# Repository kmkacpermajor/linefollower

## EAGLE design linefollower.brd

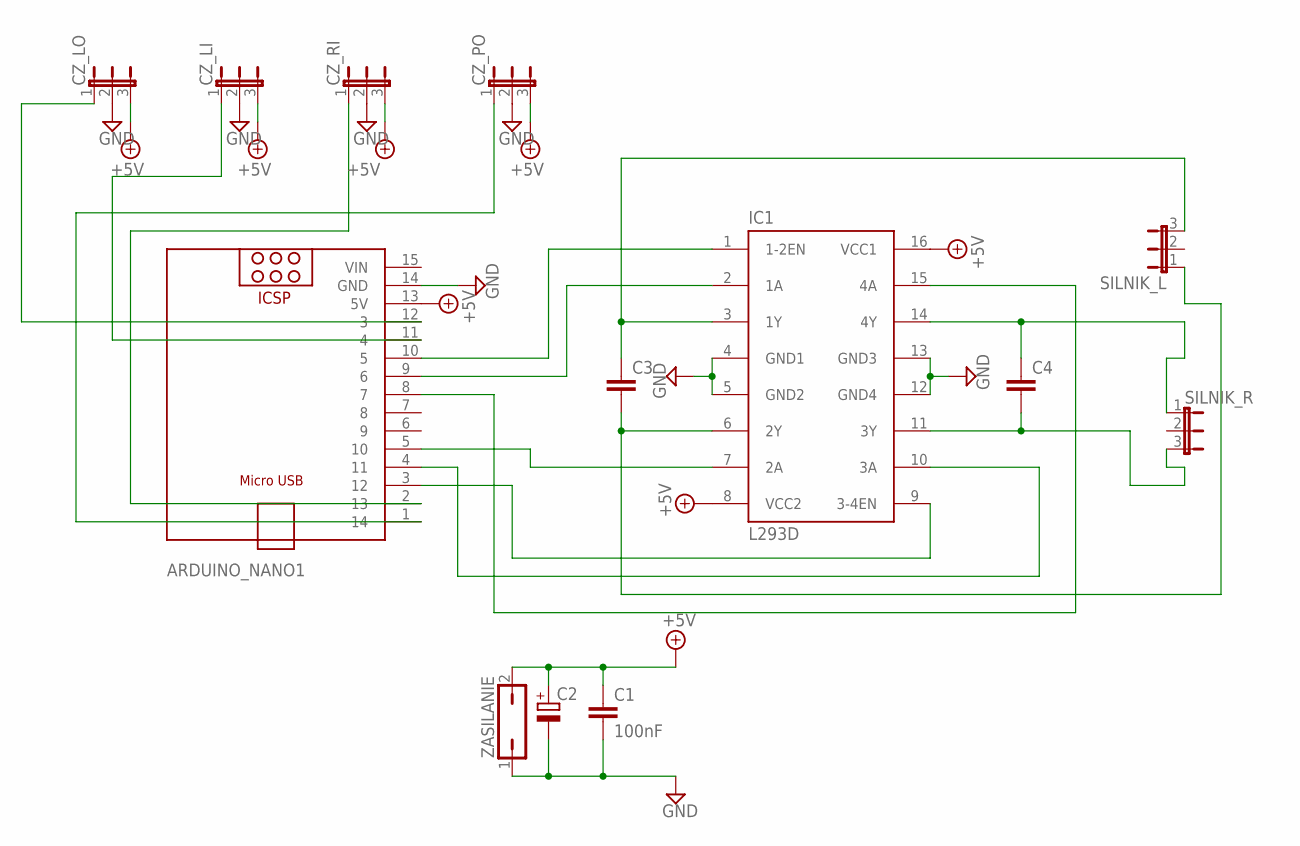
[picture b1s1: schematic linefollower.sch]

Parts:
ARDUINO_NANO1: MH-TINY
C1: 100nF; C025-025X050
C2: CPOL-EUE3.5-8; E3,5-8
C3, C4: C-EU050-025X075; C050-025X075
CZ_LI: JP2E; JP2
CZ_LO: JP2E; JP2
CZ_PO: JP2E; JP2
CZ_RI: JP2E; JP2
IC1: L293D; DIL16
SILNIK_L: JP2E; JP2
SILNIK_R: JP2E; JP2
ZASILANIE: JP1Q; JP1

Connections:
+5V: ARDUINO_NANO1.13 (5V), C1.1, C2.+, CZ_LI.3, CZ_LO.3, CZ_PO.3, CZ_RI.3, IC1.8 (VCC2), IC1.16 (VCC1), ZASILANIE.2
GND: ARDUINO_NANO1.14 (GND), C1.2, C2.-, CZ_LI.2, CZ_LO.2, CZ_PO.2, CZ_RI.2, IC1.4 (GND1), IC1.5 (GND2), IC1.12 (GND4), IC1.13 (GND3), ZASILANIE.1
unnamed: ARDUINO_NANO1.12 (3), CZ_LO.1
unnamed: ARDUINO_NANO1.1 (14), CZ_PO.1
unnamed: ARDUINO_NANO1.2 (13), CZ_RI.1
unnamed: C3.1, IC1.3 (1Y), SILNIK_L.3
unnamed: C3.2, IC1.6 (2Y), SILNIK_L.1
unnamed: C4.1, IC1.14 (4Y), SILNIK_R.1
unnamed: ARDUINO_NANO1.10 (5), IC1.1 (1-2EN)
unnamed: ARDUINO_NANO1.9 (6), IC1.2 (1A)
unnamed: ARDUINO_NANO1.5 (10), IC1.7 (2A)
unnamed: ARDUINO_NANO1.8 (7), IC1.15 (4A)
unnamed: ARDUINO_NANO1.4 (11), IC1.10 (3A)
unnamed: ARDUINO_NANO1.3 (12), IC1.9 (3-4EN)
unnamed: C4.2, IC1.11 (3Y), SILNIK_R.3
unnamed: ARDUINO_NANO1.11 (4), CZ_LI.1
VIN: ARDUINO_NANO1.15 (VIN)

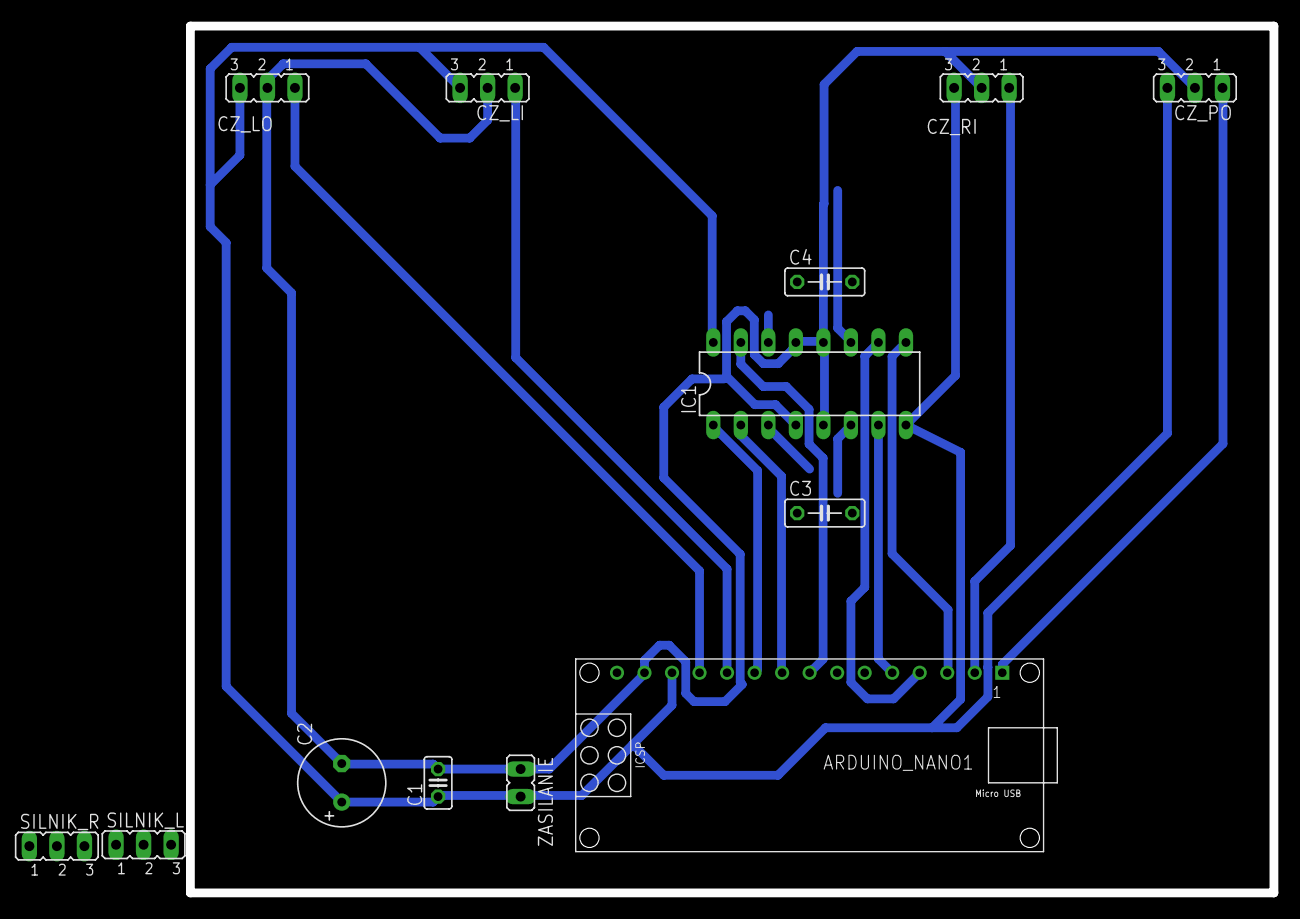
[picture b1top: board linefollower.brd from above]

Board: 2 copper layers, 100.0 x 80.0 mm, 13 parts (0 on the bottom side), 16 nets.

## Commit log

2023-04-08 Add all files
2023-04-08 Update pins
